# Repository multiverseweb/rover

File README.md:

# Rover Navigation Optimization System (R-NOS) 🛰

The Rover Navigation Optimization System is a project by **[Tejas Gupta](https://github.com/multiverseweb)** and **[Ojas Gupta](https://github.com/ojas-git)** developed under the guidance of **`Prof. Bindu Garg`**, HOD, CSE & CSBS, Bharati Vidyapeeth University, College of Engineering, Pune. It is a scaled-down prototype designed to explore real-time environmental monitoring and data-driven decision-making. The project focuses on collecting temperature and humidity readings to analyze climate conditions and detect anomalies that could impact autonomous navigation.

#### Table of Contents
| [Research Hypothesis](#research-hypothesis) | [Objective](#objective) | [Components](#components) | [Circuit](#circuit) | [Snapshots](#project-snapshots) | [Dataset](#dataset) | [ThingSpeak](#data-visualised-on-thingspeak) | [License](#license) |
|-|-|-|-|-|-|-|-|

## Research Hypothesis
A scaled-down Rover prototype can effectively collect temperature and humidity data, demonstrating how real-time environmental monitoring can be used for autonomous navigation, climate analysis, and anomaly detection.  

By analyzing the collected data, we aim to identify trends, evaluate sensor accuracy, and explore potential improvements in robotic exploration. This includes assessing response time, consistency, and anomalies caused by external factors like human interference or sudden environmental changes.  

## Objective
- To explore potential improvements in robotic exploration through data-driven insights.
- Collect and transmit thermal data wirelessly to a computer.
- Detect obstacles using ultrasonic sensors.
- Indicate path changes via buzzer and LED.
- Safeguard navigation based on temperature and obstacles.
- Log and analyze data on a laptop using ThingSpeak.

## Components

| Category | Component |
|-|-|
| Microcontroller and Communication |ESP32 / Wroom 32D |
| Sensors | HC-SR04 Ultrasonic Sensor (Obstacle detection), DHT22 (Temperature sensor) |
| Circuit and Indicators | PCB (For circuit connections), Buzzer & LED (For warnings and path indication) |
| Power Supply | Lithium-ion battery (18650), Battery charger |
| Display | OLED Display (0.96" or 1.3", SSD1306/SH1106, I2C/SPI) |
| Data Handling | Data will be transmitted and analyzed using ThingSpeak. The Arduino API will be used for interfacing and control. |

## Circuit

|  |
|-|

## Project Snapshots

|  |
|-|

## Environmental Sensor Readings from Rover Prototype

## Dataset
| |  |  |
|-|-|-|

### What the Data Shows
This dataset contains `5,400` timestamped temperature and humidity readings collected over a period of `3` hours and logged every `2` seconds by the rover’s onboard DHT22 sensor. The data highlights:
- Gradual fluctuations in environmental conditions.
- Notable temperature spikes ``(~10°C)`` introduced using a lighter to test sensor response.
- Stable humidity levels with minor deviations due to air circulation or sensor drift.

### Notable Findings
- **Controlled Temperature Spikes:** Short bursts of heat resulted in clear temperature increases `(~10°C)`, demonstrating the sensor's ability to detect and log transient changes.
- **Humidity Stability:** Humidity levels remained within a narrow range, confirming minimal impact from applied temperature fluctuations.
- **Gradual Environmental Variations:** Small temperature and humidity shifts were observed, likely due to ambient conditions and ventilation effects.

### How the Data Was Gathered
- **Sensor Used:** DHT22 (for temperature & humidity).
- **Data Collection Frequency:** Logged every few seconds.
- **Controlled Testing:** Heat spikes added using a lighter to simulate external interference.
- **Data Transmission:** Logged in real-time via wireless communication to a laptop.

### Data Visualised on ThingSpeak

|  |
|-|

| [View Live](https://thingspeak.mathworks.com/channels/2890599) |
|-|

### How to Interpret and Use the Data
- **Identify Trends:** Observe temperature and humidity variations over time.
- **Detect Anomalies:** Locate sharp temperature spikes (`~10°C` increases) caused by external heating.
- **Compare Sensor Performance:** Evaluate how quickly temperature normalizes after a spike.
- **Develop Predictive Models:** Train machine learning models to predict environmental changes.

| View [code/data_analysis.ipynb](code/data_analysis.ipynb) for more |
|-|

### Potential Applications
- **Autonomous Environment Monitoring:** Detecting and responding to environmental anomalies.
- **Sensor Calibration & Validation:** Testing DHT22 sensor accuracy under different conditions.
- **Climate Simulation & Research:** Indoor climate modeling & environmental trend analysis.
- **Robotics & AI:** Training AI for automated responses to climate fluctuations.

## License

This project is open-source under the [CC BY 4.0](https://github.com/multiverseweb/rover/blob/main/LICENSE.md).

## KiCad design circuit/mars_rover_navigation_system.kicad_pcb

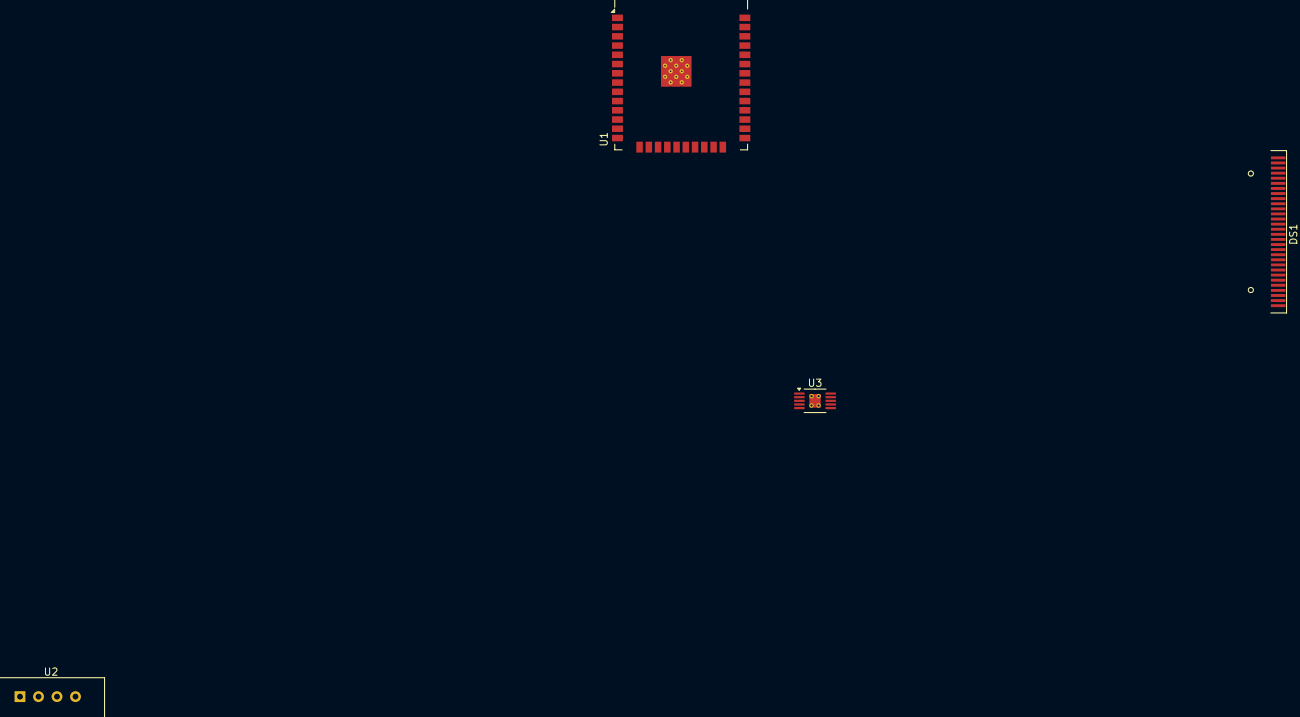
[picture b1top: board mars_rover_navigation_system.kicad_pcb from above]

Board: 2 copper layers, 4 parts (0 on the bottom side), 6 nets, no tracks yet.

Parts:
DS1: OLED-128O064D
U1: ESP32-WROOM-32
U2: AM2302; ASAIR_AM2302_P2.54mm_Vertical
U3: BQ24090DGQ; HVSSOP-10-1EP_3x3mm_P0.5mm_EP1.57x1.88mm_ThermalVias

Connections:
GNDPWR: DS1.1 (GND), DS1.30 (GND), U1.1 (GND), U1.15 (GND), U1.38 (GND), U1.39 (GND), U2.3 (GND), U2.4 (GND), U3.1 (IN)
unnamed: U3.3 (VSS), U3.11 (VSS)
unnamed: U1.2 (VDD), U2.1 (VDD)
unnamed: DS1.28 (VCC), U1.3 (EN)
unnamed: U1.22 (SDI/SD1), U2.2 (SDA)
unnamed: U1.5 (SENSOR_VN), U3.10 (OUT)

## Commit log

2025-03-11 fixed circuit
2025-03-12 updated code
2025-03-20 updated data
2025-03-20 coloured data
2025-03-21 Update LICENSE
2025-03-21 Rename LICENSE to LICENSE.md
2025-03-22 added notebook
2025-03-23 Rename rover.png to images/rover.png
2025-03-24 added thingspeak

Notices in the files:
README.md:
License: CC BY 4.0
